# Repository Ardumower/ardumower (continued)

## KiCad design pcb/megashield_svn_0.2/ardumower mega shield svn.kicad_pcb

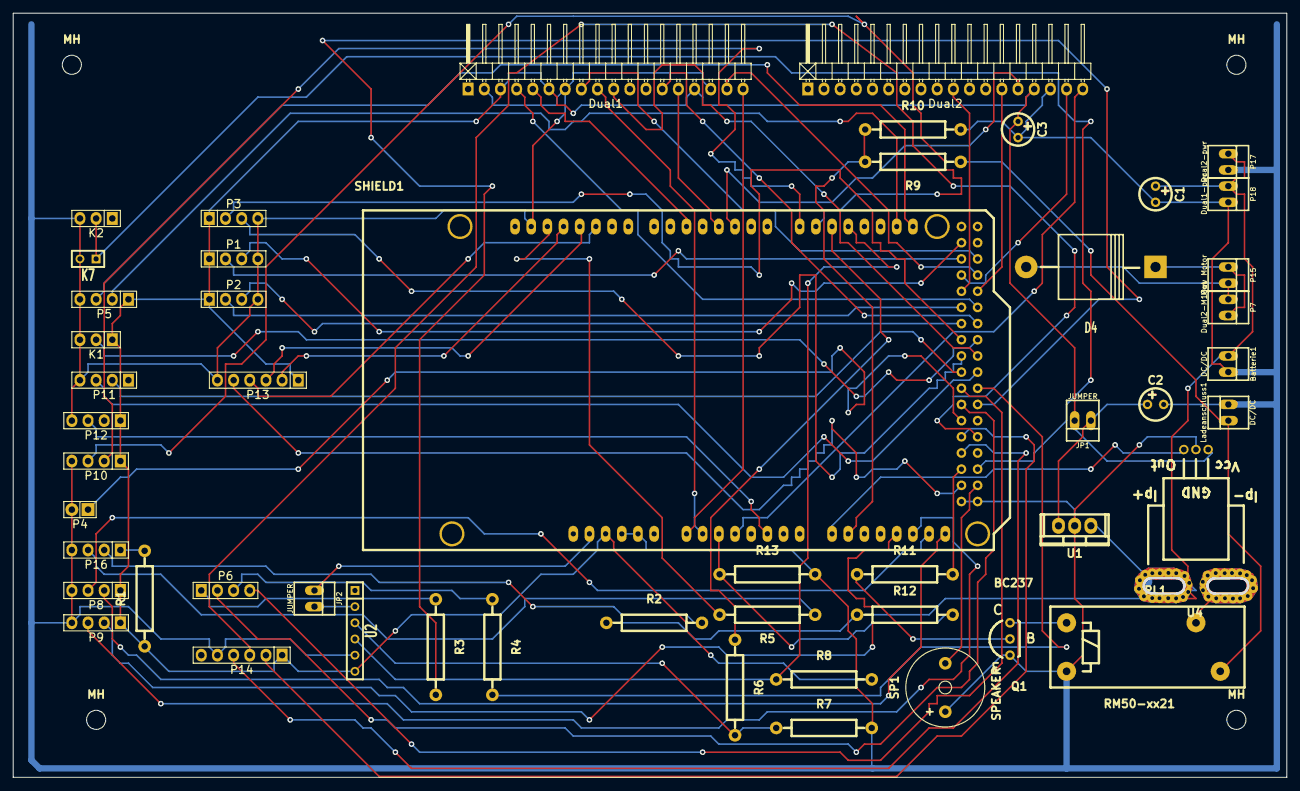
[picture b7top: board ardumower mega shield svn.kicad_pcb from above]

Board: 2 copper layers, 200.0 x 120.0 mm, 55 parts (0 on the bottom side), 71 nets.

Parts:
Batterie1: DC/DC; PINHEAD1-2
C1, C2: 10uF; Elko_vert_DM5_RM2-5
C3: 0,1uF; Elko_vert_DM5_RM2-5
D4: MBR1045 schotky; Diode_P600_Horizontal
Dual1, Dual2: MC33926; Pin_Header_Angled_1x18
JP1, JP2: JUMPER; PINHEAD1-2
K1: Tilt sens; Pin_Header_Straight_1x03
K2: Led-Button; Pin_Header_Straight_1x03
K7: CONN_01X02; SIL-2
Ladeanschluss1: DC/DC; PINHEAD1-2
MH: MountingHole_3mm_RevA_Date21Jun2010; MountingHole_3mm
MH#2, MH#3, MH#4: MountingHole_3mm_RevA_Date21Jun2010; MountingHole_3mm
P1: Sonar C; Pin_Header_Straight_1x04
P2: Sonar R; Pin_Header_Straight_1x04
P3: Sonar L; Pin_Header_Straight_1x04
P4: Rain; Pin_Header_Straight_1x02
P5: I2C; Pin_Header_Straight_1x04
P6: Lawn sens; Pin_Header_Straight_1x04
P7: Dual2-M1Out; PINHEAD1-2
P8: ODO Right; Pin_Header_Straight_1x04
P9: ODO Left; Pin_Header_Straight_1x04
P10: GPS; Pin_Header_Straight_1x04
P11: Bumper; Pin_Header_Straight_1x04
P12: Perimeter; Pin_Header_Straight_1x04
P13: RC Remote; Pin_Header_Straight_1x06
P14: User switch; Pin_Header_Straight_1x06
P15: Mow Motor; PINHEAD1-2
P16: CONN_01X04; Pin_Header_Straight_1x04
P17: Dual2-pwr; PINHEAD1-2
P18: Dual1-pwr; PINHEAD1-2
Q1: BC237; TO-92-Bipolar-inline-wide-EBC
R1: 470r; Resistor_Horizontal_RM15mm
R2, R11: 2k2; Resistor_Horizontal_RM15mm
R3, R4: 2M2; Resistor_Horizontal_RM15mm
R5, R6: 470R; Resistor_Horizontal_RM15mm
R7, R8: 1K; Resistor_Horizontal_RM15mm
R9, R12: 47K; Resistor_Horizontal_RM15mm
R10, R13: 5K; Resistor_Horizontal_RM15mm
RL1: RM50-xx21; Relais_SPDT_Schrack-RP-II-1_RM3-5mm
SHIELD1: ARDUINO_MEGA_SHIELD; ARDUINO MEGA SHIELD
SP1: SPEAKER; Buzzer_12x9.5RM7.6
U1: 7805; TO-220
U2: HC05_MODULE_ardumower_; SIL-6
U4: ACS754SCB-200; Allegro_HallSensor_Package-CB-PFF_05Jun2012

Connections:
+3.3V: JP2.1, SHIELD1.3V3
+5V: C3.1, Dual1.3, Dual1.6, Dual1.15, Dual2.15, JP1.2, K1.1, P1.1, P2.1, P3.1, P5.1, P8.1, P9.1, P10.1, P12.1, P13.1, P14.1, R1.1, R8.2, SHIELD1.5V, U2.6, U4.1
+24V: Batterie1.1, C1.1, P17.1, P18.1, R2.1, R12.1, U1.VI, U4.4
GND: Batterie1.2, C1.2, C2.2, C3.2, Dual1.2, Dual1.7, Dual1.16, Dual2.16, K1.3, K2.3, K7.2, Ladeanschluss1.2, P1.4, P2.4, P3.4, P4.2, P5.4, P8.4, P9.4, P10.4, P11.4, P12.4, P13.6, P14.5, P16.4, P17.2, P18.2, Q1.E, R7.2, R10.2, R13.2, RL1.A2, SHIELD1.GND1, SHIELD1.GND2, SHIELD1.GND3, SHIELD1.GND4, SHIELD1.GND5, SP1.1, U1.GND, U2.5, U4.2
GPS_RX: P10.2, SHIELD1.14
GPS_TX: P10.3, SHIELD1.15
Led-Status: P16.3, R5.1
LedPin-5v: P16.1, R1.2
LedPin-24v: P16.2, R2.2
unnamed: C2.1, JP1.1, U1.VO
unnamed: D4.1, P7.1, P15.2
unnamed: D4.2, P7.2, P15.1
unnamed: JP2.2, U2.2
unnamed: Ladeanschluss1.1, R9.1, RL1.14
unnamed: P6.1, R3.1
unnamed: P6.3, R4.1
unnamed: Q1.B, R11.1
unnamed: Q1.C, RL1.A1
unnamed: R6.2, R7.1, U2.3
unnamed: RL1.11, U4.5
RX2: R8.1, SHIELD1.17, U2.4
SCL: P5.3, SHIELD1.21
SDA: P5.2, SHIELD1.20
TX2: R6.1, SHIELD1.16
pinBatteryVoltage: R12.2, R13.1, SHIELD1.AD2
pinBumperLeft: P11.3, SHIELD1.39
pinBumperRight: P11.2, SHIELD1.38
pinButton: K2.2, K7.1, SHIELD1.51
pinBuzzer: SHIELD1.53, SP1.2
pinChargeCurrent: SHIELD1.AD8, U4.3
pinChargeVoltage: R9.2, R10.1, SHIELD1.AD9
pinChargingEnable: R11.2, SHIELD1.50
pinLED: R5.2, SHIELD1.13
pinLawnBackRecv: P6.2, SHIELD1.42
pinLawnBackSend: R3.2, SHIELD1.43
pinLawnFrontRecv: P6.4, SHIELD1.40
pinLawnFrontSend: R4.2, SHIELD1.41
pinMotorEnable: Dual1.10, SHIELD1.37
pinMotorLeftDir: Dual1.4, SHIELD1.31
pinMotorLeftFault: Dual1.8, SHIELD1.25
pinMotorLeftPWM: Dual1.5, SHIELD1.5
pinMotorLeftSense: Dual1.9, SHIELD1.AD1
pinMotorMowDir: Dual2.13, SHIELD1.29
pinMotorMowEnable: Dual2.10, SHIELD1.28
pinMotorMowFault: Dual2.17, SHIELD1.26
pinMotorMowPWM: Dual2.14, SHIELD1.2
pinMotorMowSense: Dual2.18, SHIELD1.AD3
pinMotorRightDir: Dual1.13, SHIELD1.33
pinMotorRightFault: Dual1.17, SHIELD1.27
pinMotorRightPWM: Dual1.14, SHIELD1.3
pinMotorRightSense: Dual1.18, SHIELD1.AD0
pinOdometryLeft: P9.2, SHIELD1.AD12
pinOdometryLeft2: P9.3, SHIELD1.AD13
pinOdometryRight: P8.2, SHIELD1.AD15
pinOdometryRight2: P8.3, SHIELD1.AD14
pinPerimeterLeft: P12.3, SHIELD1.AD5
pinRain: P4.1, SHIELD1.44
pinRemoteMow: P13.2, SHIELD1.12
pinRemoteSpeed: P13.4, SHIELD1.10
pinRemoteSteer: P13.3, SHIELD1.11
pinRemoteSwitch: P13.5, SHIELD1.52
pinSonarCenterEcho: P1.3, SHIELD1.22
pinSonarCenterTrigger: P1.2, SHIELD1.24
pinSonarLeftEcho: P3.3, SHIELD1.36
pinSonarLeftTrigger: P3.2, SHIELD1.34
pinSonarRightEcho: P2.3, SHIELD1.32
pinSonarRightTrigger: P2.2, SHIELD1.30
pinTilt: K1.2, SHIELD1.35
pinUserSwitch1: P14.2, SHIELD1.46
pinUserSwitch2: P14.3, SHIELD1.47
pinUserSwitch3: P14.4, SHIELD1.48
